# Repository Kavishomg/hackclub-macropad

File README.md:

# Kavish's Macropad Project

This is my project for the Hack Club Blueprint. i wanted a controller for my pc and some robots that i am gonna build in future. So i decided to build a custom macropad with 5 keys which i think are enough for versitility. it also features a knob and an OLED display that i think feels cool!

## How it was built:
It was my first time ever designing a pcb so i would say that its not the perfect pcb but it works. I had thought that making a pcb would be such a technical challenge for me but turns out, i actually enjoyed it and learned soooo much in the process.

I designed my 3d case in onshape. It was a pain to make everyhting fit together in perfect dimension and figure out specs of cherry mx switches.

## 1. The Full Assembly

*(Note to Reviewer: This STEP file is available in the CAD folder as Macropad_Assembly.step)*

## Why I Built This
When i got my dream pc, i planned that i will be building a lot of cool projects. but turns out that as a student, i rarely had time to pull anything off. but when i came to know about this project, it gave me just the right kick to start working on a REAL PROJECT. This being my first project i am really excited to build it in real life now. i want to show it to my parents!!!! (i am very excited to see how this turns out)

This project combines my interests in electronics, 3D design, and embedded firmware. It features:
* Visual Feedback: A 0.91" OLED screen to display layers and modes.
* Analog Input: A Rotary Encoder for precise volume or scrolling control.
* Aesthetics: Underglow RGB lighting tucked between the switches.
* Ergonomics: A high-profile, 3D-printed case designed with enough clearances for Cherry MX switches.

## 2. The Electronics (Schematic)
I designed it using KiCad. it was confusing at first to figure out what goes where and which pin to connect to what component. But i managed to map everything without conflicts.

* **MCU:** Seeed XIAO RP2040
* **Display Protocol:** I2C (Pins D4/D5)
* **Lighting:** PWM/Data driver for SK6812 LEDs

## 3. The PCB Design
It was suggested to me that i use ground pour but while doing it i encountered a lot of errors. given the approaching deadline, i went with manually connecting the grounds together.

* Mounting: 4x M3 Holes aligned to the case standoffs.
* Placement: Symmetric layout with the Rotary Encoder as the centerpiece.
* Lighting: LEDs are strategically placed in the gaps between switches to create a diffuse glow.

## 4. The Mechanical Case
Designed in Onshape. This is a 3D-printable case featuring a **1.6mm integrated top plate** to perfectly snap-fit Cherry MX switches.

* Material: PLA / PETG
* **Access:** Precision cutout for USB-C cable.

## 5. Bill of Materials (BOM)
These are based on the allowed parts list submitted by the community

| Component | Quantity | Description |
| :--- | :--- | :--- |
| **Microcontroller** | 1 | Seeed XIAO RP2040 |
| **Switches** | 5 | Cherry MX Style Mechanical Switches |
| **Input** | 1 | EC11 Rotary Encoder |
| **Display** | 1 | 0.91" OLED Display (I2C) |
| **Lighting** | 2 | SK6812 MINI-E RGB LEDs |
| **Case** | 1 | Custom 3D Printed Enclosure (STL/STEP provided) |
| **Hardware** | 4 | M3 Screws |

## Firmware Plan
The board will run on **KMK Firmware** (CircuitPython). This allows for dynamic key remapping and OLED layer display without recompiling code.

**Planned Keymap:**
* Encoder: Volume Up/Down (Press to Mute)
* OLED: Displays current "Layer" (e.g., Media, Editing, Gaming)
* Keys: Play/Pause, Next, Prev, Copy, Paste

### Acknowledgments
Huge thanks to the **Hack Club Blueprint** team for making hardware engineering accessible!

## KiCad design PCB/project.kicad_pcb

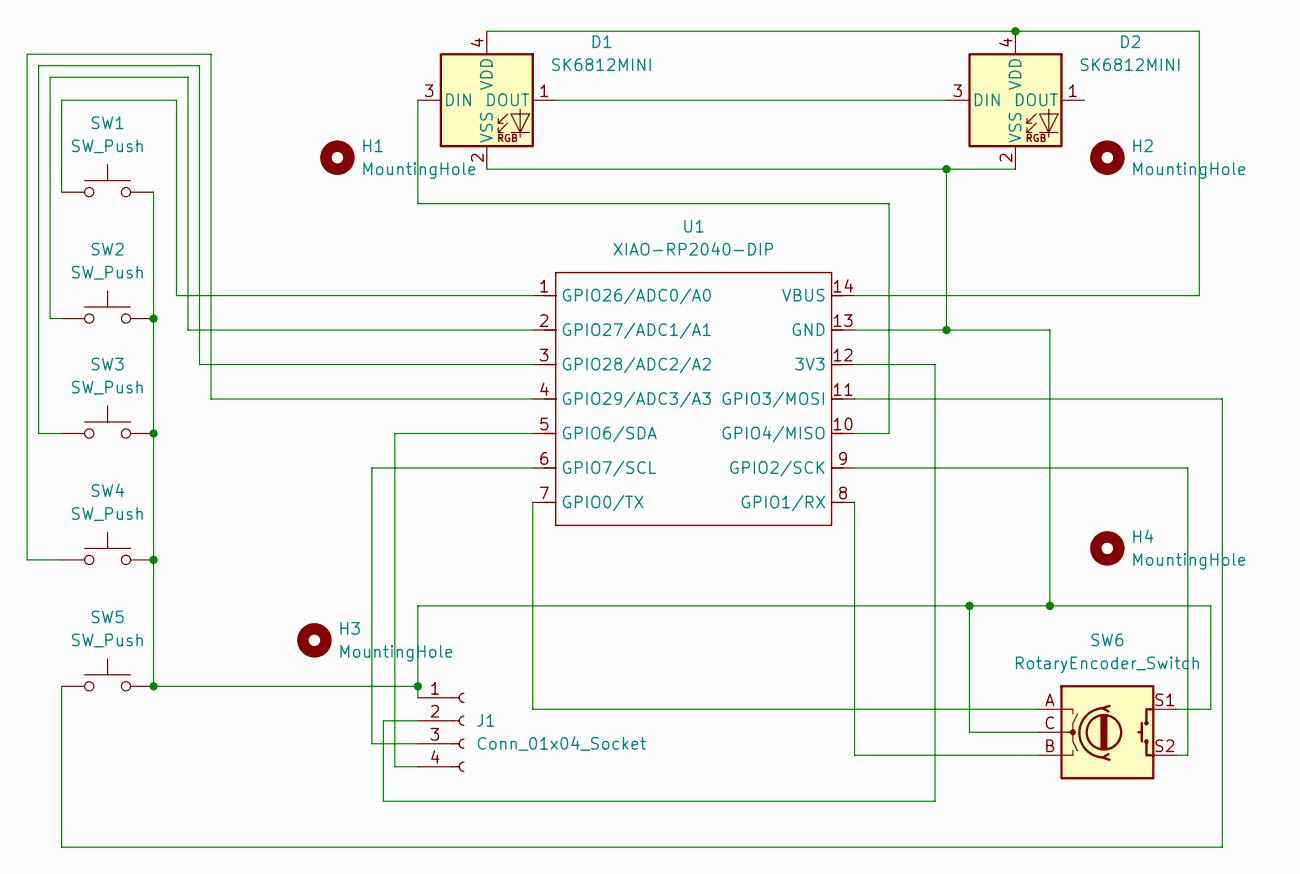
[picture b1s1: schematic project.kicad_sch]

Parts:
D1, D2: SK6812MINI; LED_SK6812MINI_PLCC4_3.5x3.5mm_P1.75mm
H1, H2, H3, H4: MountingHole; MountingHole_3.2mm_M3
J1: Conn_01x04_Socket; PinHeader_1x04_P2.54mm_Vertical
SW1, SW2, SW3, SW4, SW5: SW_Push; SW_Cherry_MX_1.00u_PCB
SW6: RotaryEncoder_Switch; RotaryEncoder_Alps_EC11E-Switch_Vertical_H20mm_MountingHoles
U1: XIAO-RP2040-DIP

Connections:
unnamed: D1.3 (DIN), U1.10 (GPIO4/MISO)
unnamed: D1.1 (DOUT), D2.3 (DIN)
unnamed: D1.4 (VDD), D2.4 (VDD), U1.14 (VBUS)
unnamed: D1.2 (VSS), D2.2 (VSS), J1.1, SW1.2, SW2.2, SW3.2, SW4.2, SW5.2, SW6.C, SW6.S1, U1.13 (GND)
unnamed: J1.2, U1.12 (3V3)
unnamed: J1.3, U1.6 (GPIO7/SCL)
unnamed: J1.4, U1.5 (GPIO6/SDA)
unnamed: SW6.A, U1.7 (GPIO0/TX)
unnamed: SW6.B, U1.8 (GPIO1/RX)
unnamed: SW6.S2, U1.9 (GPIO2/SCK)
unnamed: SW5.1, U1.11 (GPIO3/MOSI)
unnamed: SW1.1, U1.1 (GPIO26/ADC0/A0)
unnamed: SW2.1, U1.2 (GPIO27/ADC1/A1)
unnamed: SW3.1, U1.3 (GPIO28/ADC2/A2)
unnamed: SW4.1, U1.4 (GPIO29/ADC3/A3)

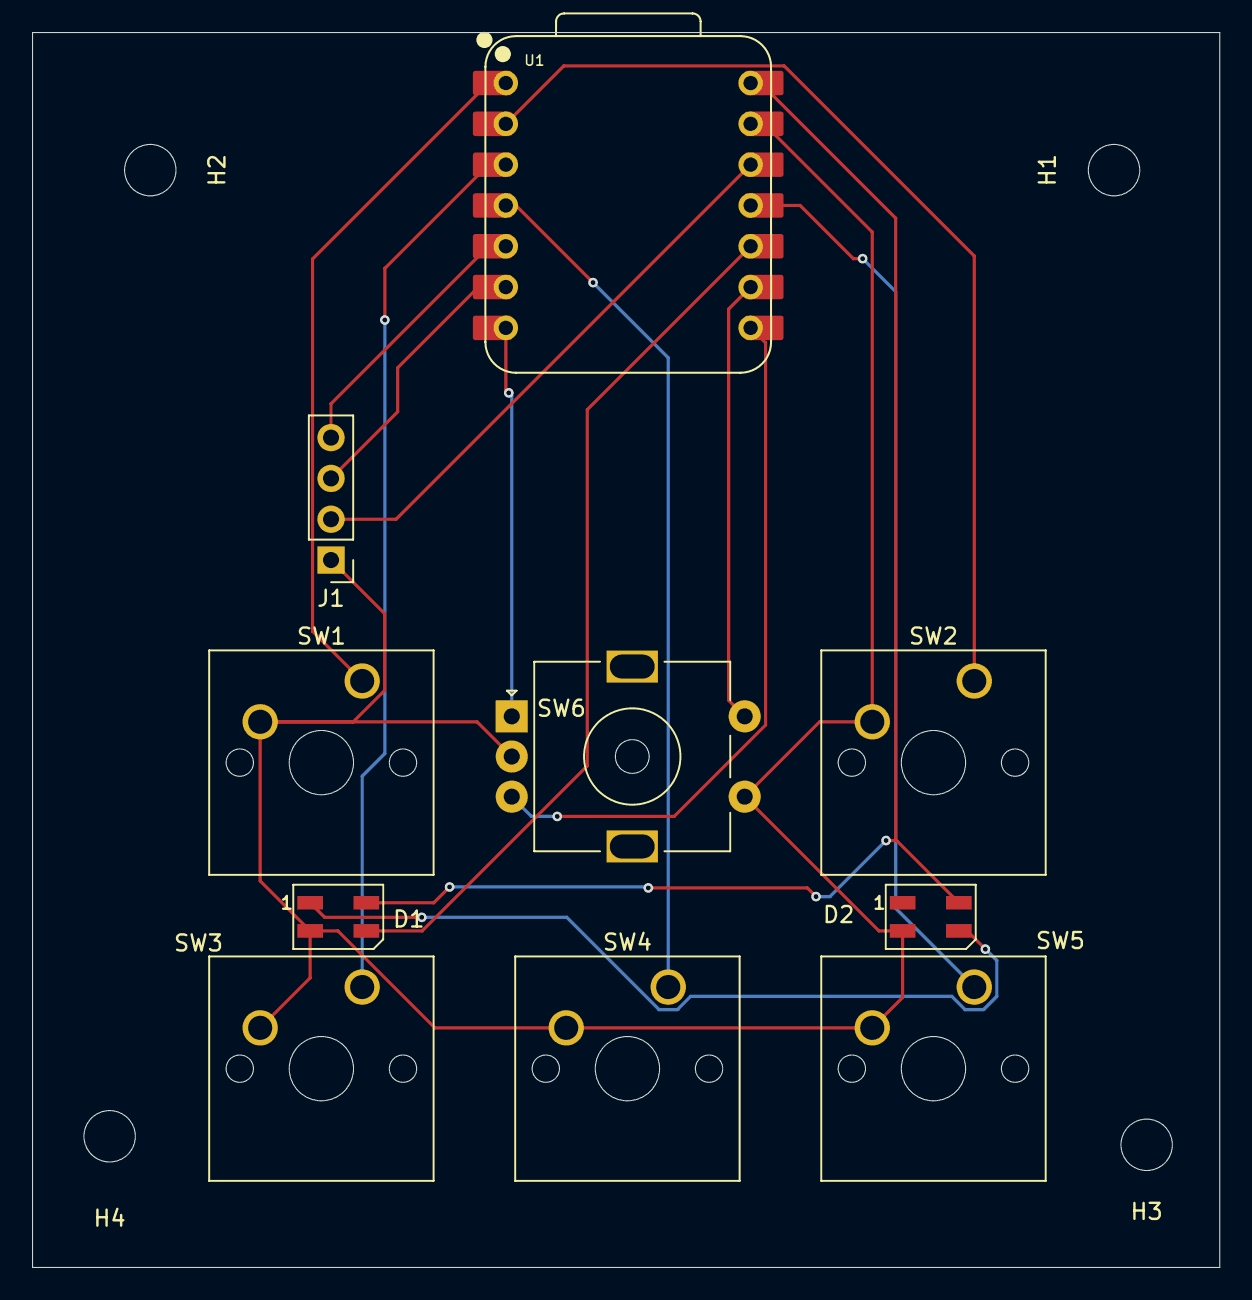
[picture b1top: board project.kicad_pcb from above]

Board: 2 copper layers, 73.9 x 76.9 mm, 14 parts (0 on the bottom side), 15 nets.

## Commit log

2025-12-05 Add initial PCB design source files
2025-12-05 Add initial CAD assembly and case design
2025-12-05 Initialize Macropad firmware with keymap and modules
2025-12-05 Add README for Orbital Control Station project
    Added detailed documentation for the Orbital Control Station project, including assembly, electronics, PCB design, mechanical case, BOM, and firmware plan.
2025-12-13 Revise README for Kavish's Macropad Project
    Updated the README to reflect project details and personal insights.
